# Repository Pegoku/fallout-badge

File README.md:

# Small Morse Code Handheld Devices

From: @Pegoku

ESP32-C3 based boards that connect to each other and let you send and receive messages using ESPNOW.

## BOM (Per PCB)

| Item           | Quantity | JLCPCB PN. |
| -------------- | -------- | ---------- |
| XIAO ESP32-C3  | 1        | N/A        |
| 100 Ω resistor | 10       | C22775     |
| Push button    | 3        | C318884    |
| 0805 Red LED   | 14       | C84256     |

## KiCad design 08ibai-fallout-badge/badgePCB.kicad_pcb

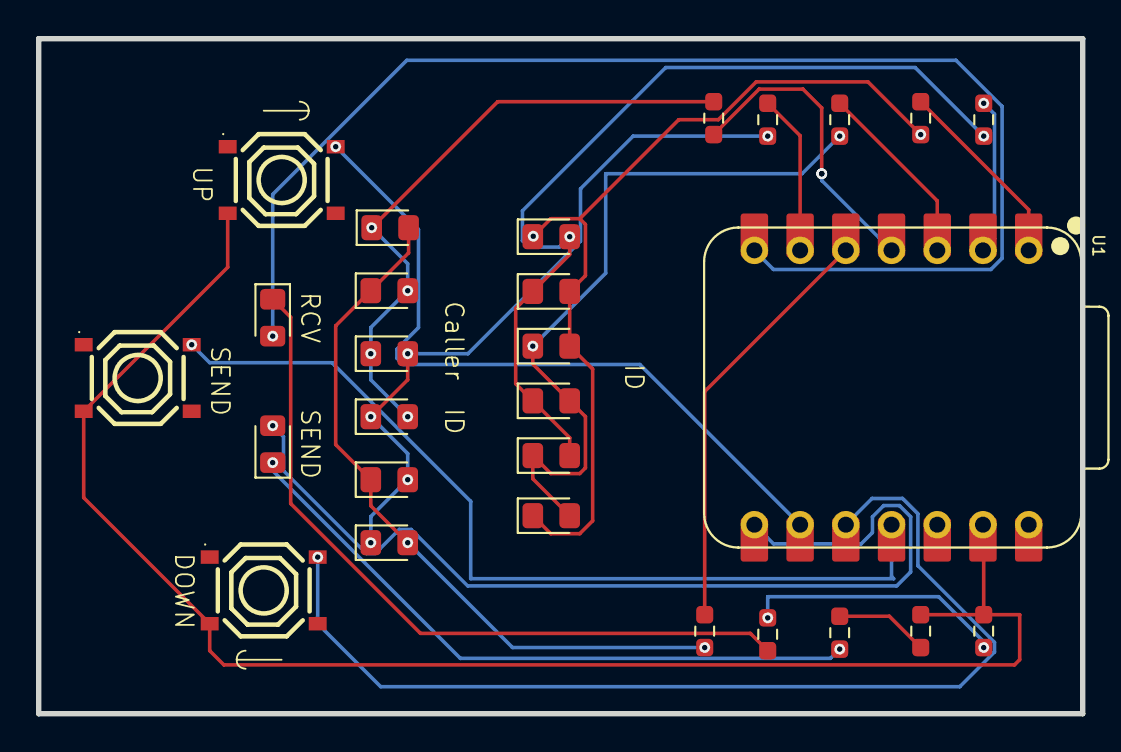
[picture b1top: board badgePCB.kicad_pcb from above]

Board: 2 copper layers, 58.0 x 37.5 mm, 28 parts (0 on the bottom side), 22 nets.

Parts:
D1, D2, D3, D4, D5, D6, D7, D8, D9, D10, D11, D12, D13, D14: LED; LED_0805_2012Metric_Pad1.15x1.40mm_HandSolder
R1, R2, R3, R4, R5, R6, R7, R8, R9, R10: 100R; R_0603_1608Metric_Pad0.98x0.95mm_HandSolder
SW2, SW3: TS-1187A-B-A-B; SW-SMD_4P-L5.1-W5.1-P3.70-LS6.5-TL_H1.5
U1: XIAO-ESP32-C3-DIP; XIAO-ESP32C3-DIP
UP: TS-1187A-B-A-B; SW-SMD_4P-L5.1-W5.1-P3.70-LS6.5-TL_H1.5

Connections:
Action: SW3.2 (B), U1.11 (GPIO10/D10/MOSI)
GND: R9.2, R10.2, SW2.3 (C), SW3.3 (C), U1.13 (GND), UP.3 (C)
IDDown: SW2.2 (B), U1.10 (GPIO9/D9/MISO)
IDUp: U1.9 (GPIO8/D8/SCK), UP.2 (B)
MID1: R2.2, U1.1 (GPIO2/A0/D0)
MID2: R1.2, U1.2 (GPIO3/A1/D1)
MID3: R3.2, U1.3 (GPIO4/A2/D2)
unnamed: D1.2 (A), D2.1 (K), D4.1 (K), D5.2 (A), R1.1
unnamed: D1.1 (K), D2.2 (A), D3.2 (A), D6.1 (K), R2.1
unnamed: D3.1 (K), D4.2 (A), D5.1 (K), D6.2 (A), R3.1
unnamed: D7.1 (K), D8.2 (A), D9.1 (K), D10.2 (A), R5.1
unnamed: D9.2 (A), D10.1 (K), D11.2 (A), D12.1 (K), R4.1
unnamed: D7.2 (A), D8.1 (K), D11.1 (K), D12.2 (A), R6.1
unnamed: D13.1 (K), R7.1
unnamed: D14.1 (K), R8.1
unnamed: R8.2, R9.1
unnamed: R7.2, R10.1
RLED: D13.2 (A), U1.7 (GPIO21/D6/TX)
SID1: R5.2, U1.4 (GPIO5/A3/D3)
SID2: R6.2, U1.5 (GPIO6/D4/SDA)
SID3: R4.2, U1.6 (GPIO7/D5/SCL)
SLED: D14.2 (A), U1.8 (GPIO20/D7/RX)

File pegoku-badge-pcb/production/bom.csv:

Designator,Footprint,Quantity,Value,LCSC Part #
"D1, D10, D11, D12, D13, D14, D2, D3, D4, D5, D6, D7, D8, D9",0805,14,LED,C84256
"R1, R10, R2, R3, R4, R5, R6, R7, R8, R9",0603,10,100R,C22775
"SW1, SW2, SW3",SW-SMD_4P-L5.1-W5.1-P3.70-LS6.5-TL_H1.5,3,TS-1187A-B-A-B,C318884
U1,XIAO-ESP32C3-SMD,1,XIAO-ESP32-C3-DIP,

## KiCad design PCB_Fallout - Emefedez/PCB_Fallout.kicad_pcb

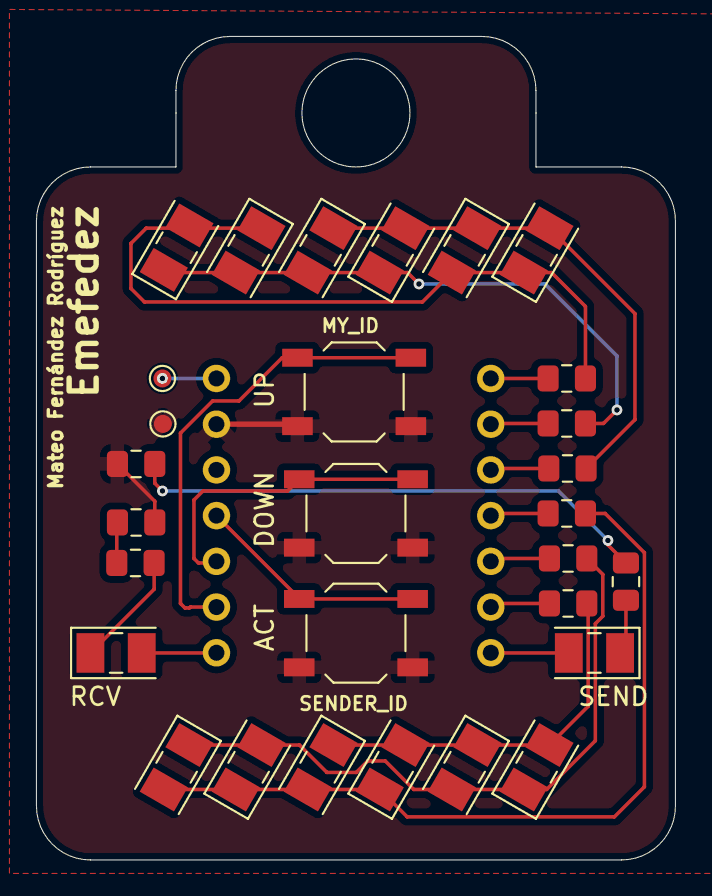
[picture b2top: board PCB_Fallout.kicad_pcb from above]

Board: 2 copper layers, 35.5 x 45.8 mm, 30 parts (1 on the bottom side), 23 nets.

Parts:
LED0, LED1, LED2, LED3, LED4, LED5, LED6, LED7, LED8, LED9, LED10, LED11, LED12, LED13: KT-0805Y; LED_PLCC-2_3x2mm_KA
R0, R1, R2, R3, R4, R5, R6, R7, R8, R9: 100ohm; C_0805_2012Metric_Pad1.18x1.45mm_HandSolder
SW1, SW2, SW3: SW_Push; SW_SPST_TL3342
TP1, TP2: TestPoint; TestPoint_Pad_D1.0mm
U1: XIAO-ESP32-C3-DIP

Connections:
ACT: SW3.1, U1.11 (GPIO10/D10/MOSI)
DOWN: SW2.1, U1.10 (GPIO9/D9/MISO)
GND: R6.1, R8.1, SW1.2, SW2.2, SW3.2, TP2.1 (1_1), U1.13 (GND)
MY_ID0: R0.1, U1.1 (GPIO2/A0/D0)
MY_ID1: R1.2, U1.2 (GPIO3/A1/D1)
MY_ID2: R2.1, U1.3 (GPIO4/A2/D2)
unnamed: LED0.2 (A), LED1.1 (K), LED4.2 (A), LED5.1 (K), R0.2
unnamed: LED0.1 (K), LED1.2 (A), LED2.2 (A), LED3.1 (K), R1.1
unnamed: LED2.1 (K), LED3.2 (A), LED4.1 (K), LED5.2 (A), R2.2
unnamed: LED6.2 (A), LED7.1 (K), LED8.2 (A), LED9.1 (K), R3.2
unnamed: LED6.1 (K), LED7.2 (A), LED10.2 (A), LED11.1 (K), R4.1
unnamed: LED8.1 (K), LED9.2 (A), LED10.1 (K), LED11.2 (A), R5.2
unnamed: LED12.1 (K), R7.2
unnamed: LED13.1 (K), R9.2
unnamed: R6.2, R7.1
unnamed: R8.2, R9.1
unnamed: TP1.1 (1_1), U1.14 (VBUS)
RCV_LED: LED13.2 (A), U1.8 (GPIO20/D7/RX)
SND_ID0: R3.1, U1.4 (GPIO5/A3/D3)
SND_ID1: R4.2, U1.5 (GPIO6/D4/SDA)
SND_ID2: R5.1, U1.6 (GPIO7/D5/SCL)
SND_LED: LED12.2 (A), U1.7 (GPIO21/D6/TX)
UP: SW1.1, U1.9 (GPIO8/D8/SCK)
